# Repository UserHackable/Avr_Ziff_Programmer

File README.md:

## Avr ZIFF Programmer

This simple utilitarian board makes use of a Ziff Socket and AVR ICSP headers to enable the programming of four different

* ATtiny85
* ATtiny84
* ATtiny2313
* ATmega328

It also has a FTDI adapter that works with the ATmega328

very handy for flashing a bunch of chips to put in kits. 

You can 

## AvrZiffProgrammer 

### Board dimensions

* (240000, 129997) original units
* (2.4000, 1.3000) inches
* (60.9600, 33.0192) mm

| Front | Back |
| --- | --- |
|  |  |

## Breadboard_ICSP 

### Board dimensions

* (40000, 50000) original units
* (0.4000, 0.5000) inches
* (10.1600, 12.7000) mm

| Front | Back |
| --- | --- |
|  |  |

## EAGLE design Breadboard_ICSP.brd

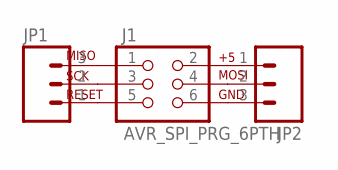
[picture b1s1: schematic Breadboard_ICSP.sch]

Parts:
J1: AVR_SPI_PRG_6PTH; 2X3
JP1, JP2: M03PTH; 1X03

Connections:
unnamed: J1.5, JP1.1
unnamed: J1.3, JP1.2
unnamed: J1.1, JP1.3
unnamed: J1.2, JP2.1
unnamed: J1.4, JP2.2
unnamed: J1.6, JP2.3

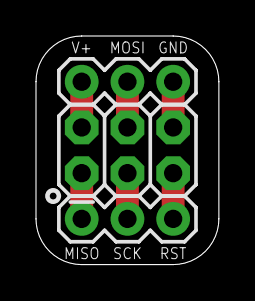
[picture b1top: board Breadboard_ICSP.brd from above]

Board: 2 copper layers, 10.2 x 12.7 mm, 3 parts (0 on the bottom side), 6 nets.

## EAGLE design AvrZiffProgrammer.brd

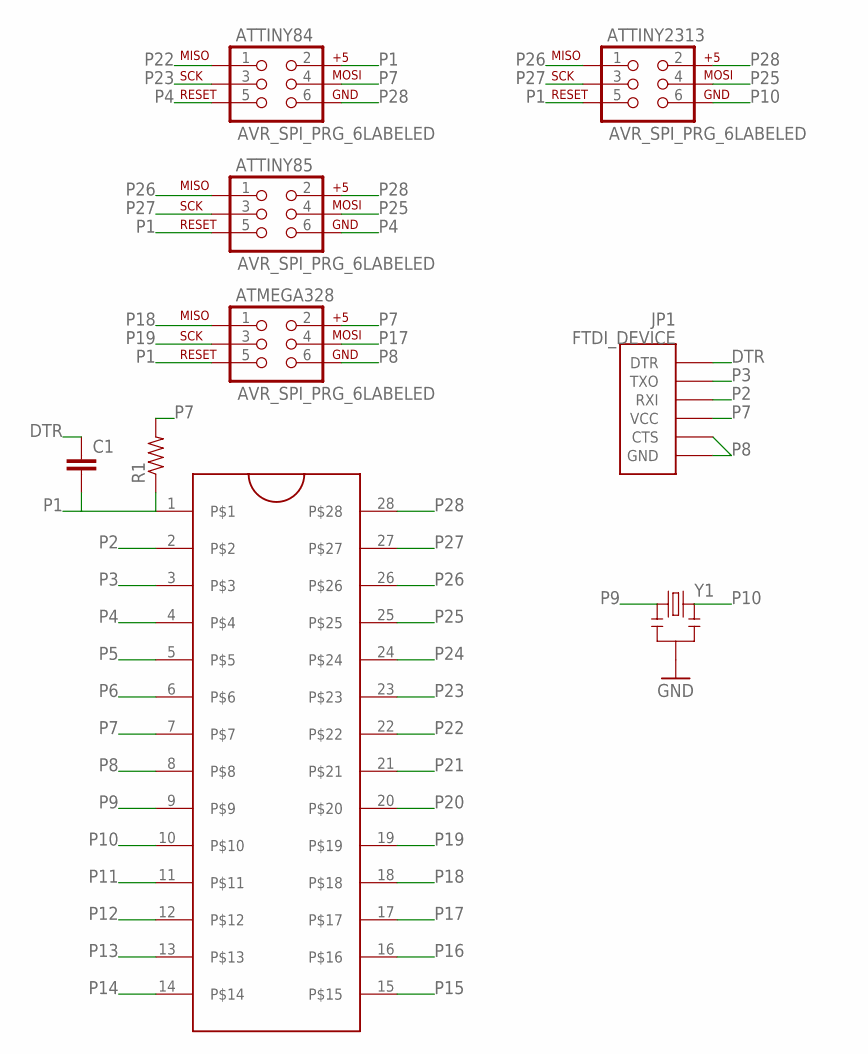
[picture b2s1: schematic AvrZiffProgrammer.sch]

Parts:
ATMEGA328: AVR_SPI_PRG_6LABELED; 2X3-NS
ATTINY84, ATTINY85, ATTINY2313: AVR_SPI_PRG_6LABELED; 2X3-NS
C1: CAPPTH; CAP-PTH-SMALL
JP1: FTDI_DEVICE; FTDI_DEVICE_SIDE
R1: RESISTORAXIAL-0.3; AXIAL-0.3
U$1: ZIFSOCKET-28-3ZIFFSOCKET-28-3; DIL28-3-ZIF_SOCKET
Y1: RESONATORPTH; RESONATOR-PTH

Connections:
DTR: C1.1, JP1.P$1 (DTR)
P1: ATMEGA328.5, ATTINY84.2, ATTINY85.5, ATTINY2313.5, C1.2, R1.P$1 (1), U$1.1
P2: JP1.P$3 (RXI), U$1.2
P3: JP1.P$2 (TXO), U$1.3
P4: ATTINY84.5, ATTINY85.6, U$1.4
P5: U$1.5
P6: U$1.6
P7: ATMEGA328.2, ATTINY84.4, JP1.P$4 (VCC), R1.P$2 (2), U$1.7
P8: ATMEGA328.6, JP1.P$5 (CTS), JP1.P$6 (GND), U$1.8, Y1.2
P9: U$1.9, Y1.1
P10: ATTINY2313.6, U$1.10, Y1.3
P11: U$1.11
P12: U$1.12
P13: U$1.13
P14: U$1.14
P15: U$1.15
P16: U$1.16
P17: ATMEGA328.4, U$1.17
P18: ATMEGA328.1, U$1.18
P19: ATMEGA328.3, U$1.19
P20: U$1.20
P21: U$1.21
P22: ATTINY84.1, U$1.22
P23: ATTINY84.3, U$1.23
P24: U$1.24
P25: ATTINY85.4, ATTINY2313.4, U$1.25
P26: ATTINY85.1, ATTINY2313.1, U$1.26
P27: ATTINY85.3, ATTINY2313.3, U$1.27
P28: ATTINY84.6, ATTINY85.2, ATTINY2313.2, U$1.28

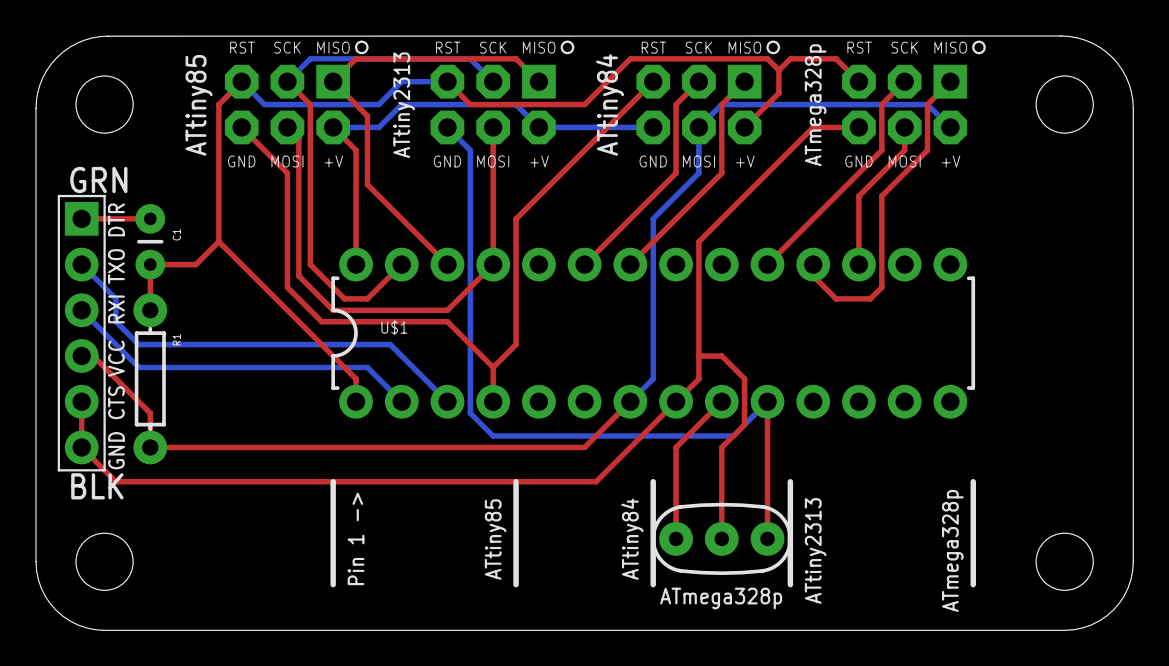
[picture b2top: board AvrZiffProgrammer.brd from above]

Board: 2 copper layers, 61.0 x 33.0 mm, 9 parts (0 on the bottom side), 18 nets.

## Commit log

2016-04-08 from Makefile

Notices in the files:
parts and their libraries:
SparkFun-Connectors: Licensing: Creative Commons ShareAlike 4.0 International - https://creativecommons.org/licenses/by-sa/4.0
